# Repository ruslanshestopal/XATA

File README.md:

# XATA
This is my home automation project. Arduino code is for the RobotDyn MEGA+WiFi R3 ATmega2560+ESP8266 board.

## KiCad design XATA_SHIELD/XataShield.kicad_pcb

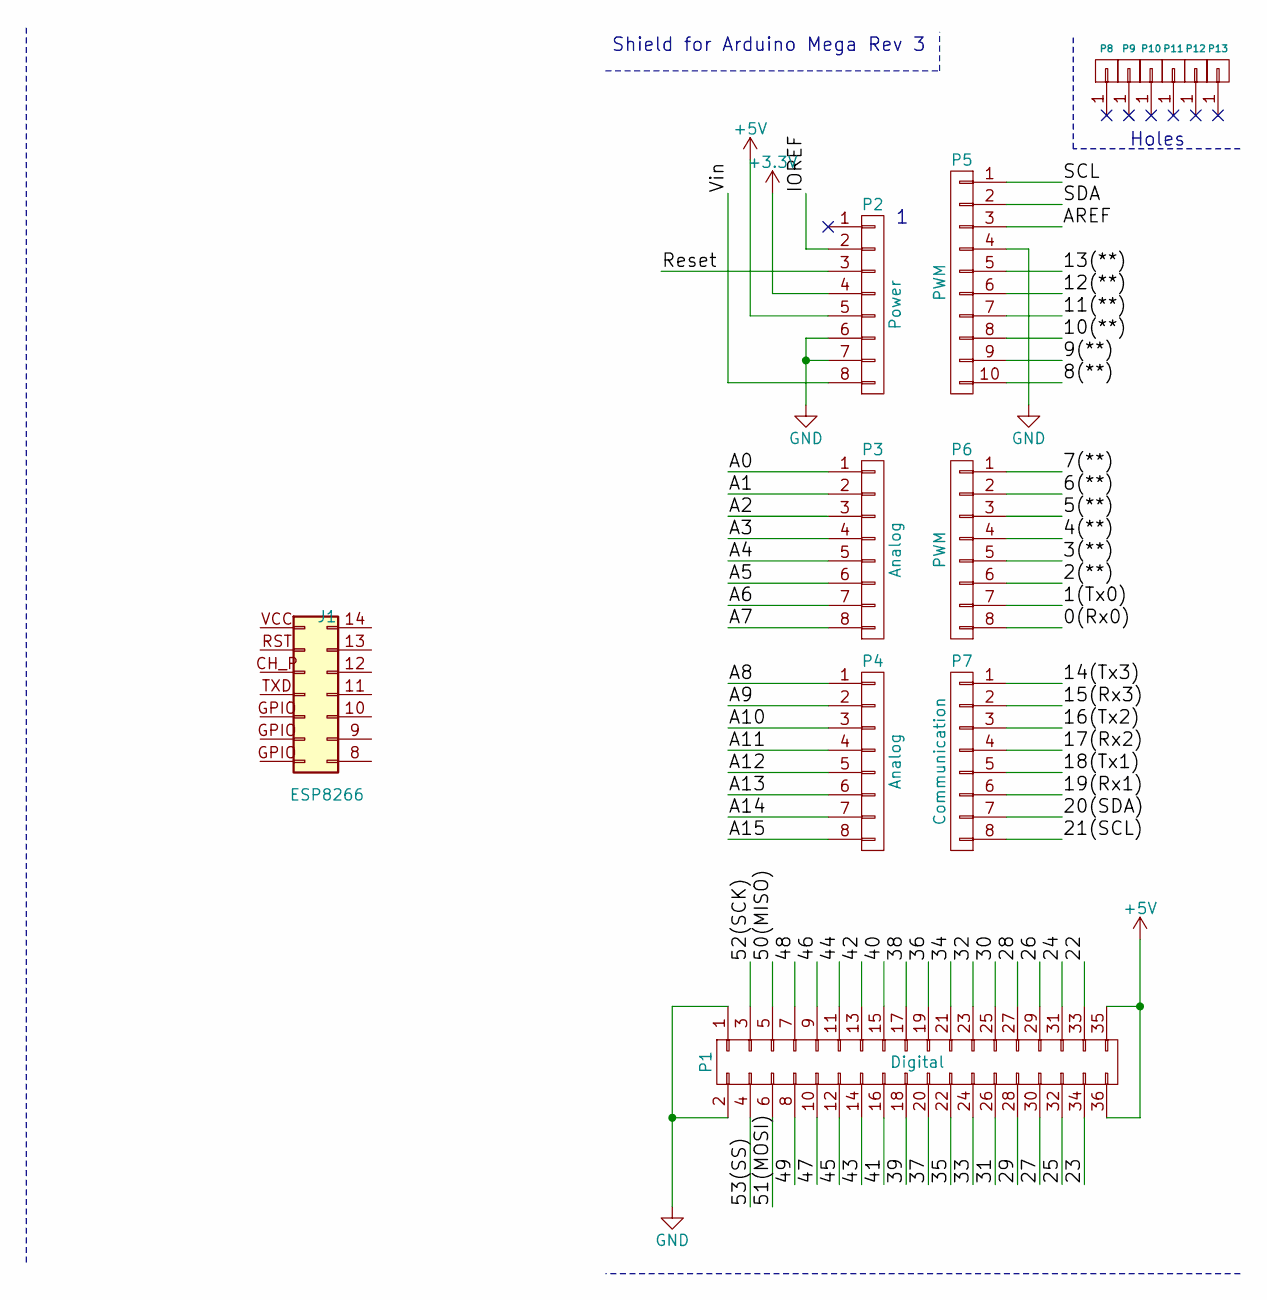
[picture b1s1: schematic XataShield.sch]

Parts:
J1: ESP8266; Pin_Header_Straight_2x07_Pitch2.54mm
P1: Digital; Socket_Strip_Arduino_2x18
P2: Power; Socket_Strip_Arduino_1x08
P3, P4: Analog; Socket_Strip_Arduino_1x08
P5: PWM; Socket_Strip_Arduino_1x10
P6: PWM; Socket_Strip_Arduino_1x08
P7: Communication; Socket_Strip_Arduino_1x08
P8, P9, P10, P11, P12, P13: CONN_01X01; Arduino_1pin

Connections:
+3V3: P2.4
+5V: P1.35, P1.36, P2.5
/0(Rx0): P6.8
/1(Tx0): P6.7
/2(**): P6.6
/3(**): P6.5
/4(**): P6.4
/5(**): P6.3
/6(**): P6.2
/7(**): P6.1
/8(**): P5.10
/9(**): P5.9
/10(**): P5.8
/11(**): P5.7
/12(**): P5.6
/13(**): P5.5
/14(Tx3): P7.1
/15(Rx3): P7.2
/16(Tx2): P7.3
/17(Rx2): P7.4
/18(Tx1): P7.5
/19(Rx1): P7.6
/20(SDA): P7.7
/21(SCL): P7.8
/22: P1.33
/23: P1.34
/24: P1.31
/25: P1.32
/26: P1.29
/27: P1.30
/28: P1.27
/29: P1.28
/30: P1.25
/31: P1.26
/32: P1.23
/33: P1.24
/34: P1.21
/35: P1.22
/36: P1.19
/37: P1.20
/38: P1.17
/39: P1.18
/40: P1.15
/41: P1.16
/42: P1.13
/43: P1.14
/44: P1.11
/45: P1.12
/46: P1.9
/47: P1.10
/48: P1.7
/49: P1.8
/50(MISO): P1.5
/51(MOSI): P1.6
/52(SCK): P1.3
/53(SS): P1.4
/A0: P3.1
/A1: P3.2
/A2: P3.3
/A3: P3.4
/A4: P3.5
/A5: P3.6
/A6: P3.7
/A7: P3.8
/A8: P4.1
/A9: P4.2
/A10: P4.3
/A11: P4.4
/A12: P4.5
/A13: P4.6
/A14: P4.7
/A15: P4.8
/AREF: P5.3
/IOREF: P2.2
/Reset: P2.3
/SCL: P5.1
/SDA: P5.2
/Vin: P2.8
GND: P1.1, P1.2, P2.6, P2.7, P5.4

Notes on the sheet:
Shield for Arduino Mega Rev 3
Holes

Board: 2 copper layers, 14 parts (0 on the bottom side), 2 nets, no tracks yet.

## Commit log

2017-10-31 Here we go
2020-11-07 Resent beta version
2020-11-08 Some cleanup
    KiCad PBS layout removed
    ESP8266 is running now over WebSocket
2023-03-04 Let's consider this version LTS
    Got rid of official nextion library.
    I2C replaced with RF24 (no more wires).
    Added MH-Z14 infrared gas module.
2023-10-04 RF24 updates
